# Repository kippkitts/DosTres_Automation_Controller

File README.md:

DosTres_Automation_Controller
=============================

The [DosTres Automation Controller](http://kippkitts.com/collections/frontpage/products/dostres-automation-controller-kk-m-23) is a shield for the Arduino Uno that allows you to control a number of high power devices.  It carries motor drivers to power 2 brush DC motors at 40v/5A as well as 3 MOSFET load switches to control high load devices (solenoids, lights, pumps, etc.).  The DosTres also allows you to drive a stepper motor in place of the DC motors.  The Eagle files for this board can be found here.

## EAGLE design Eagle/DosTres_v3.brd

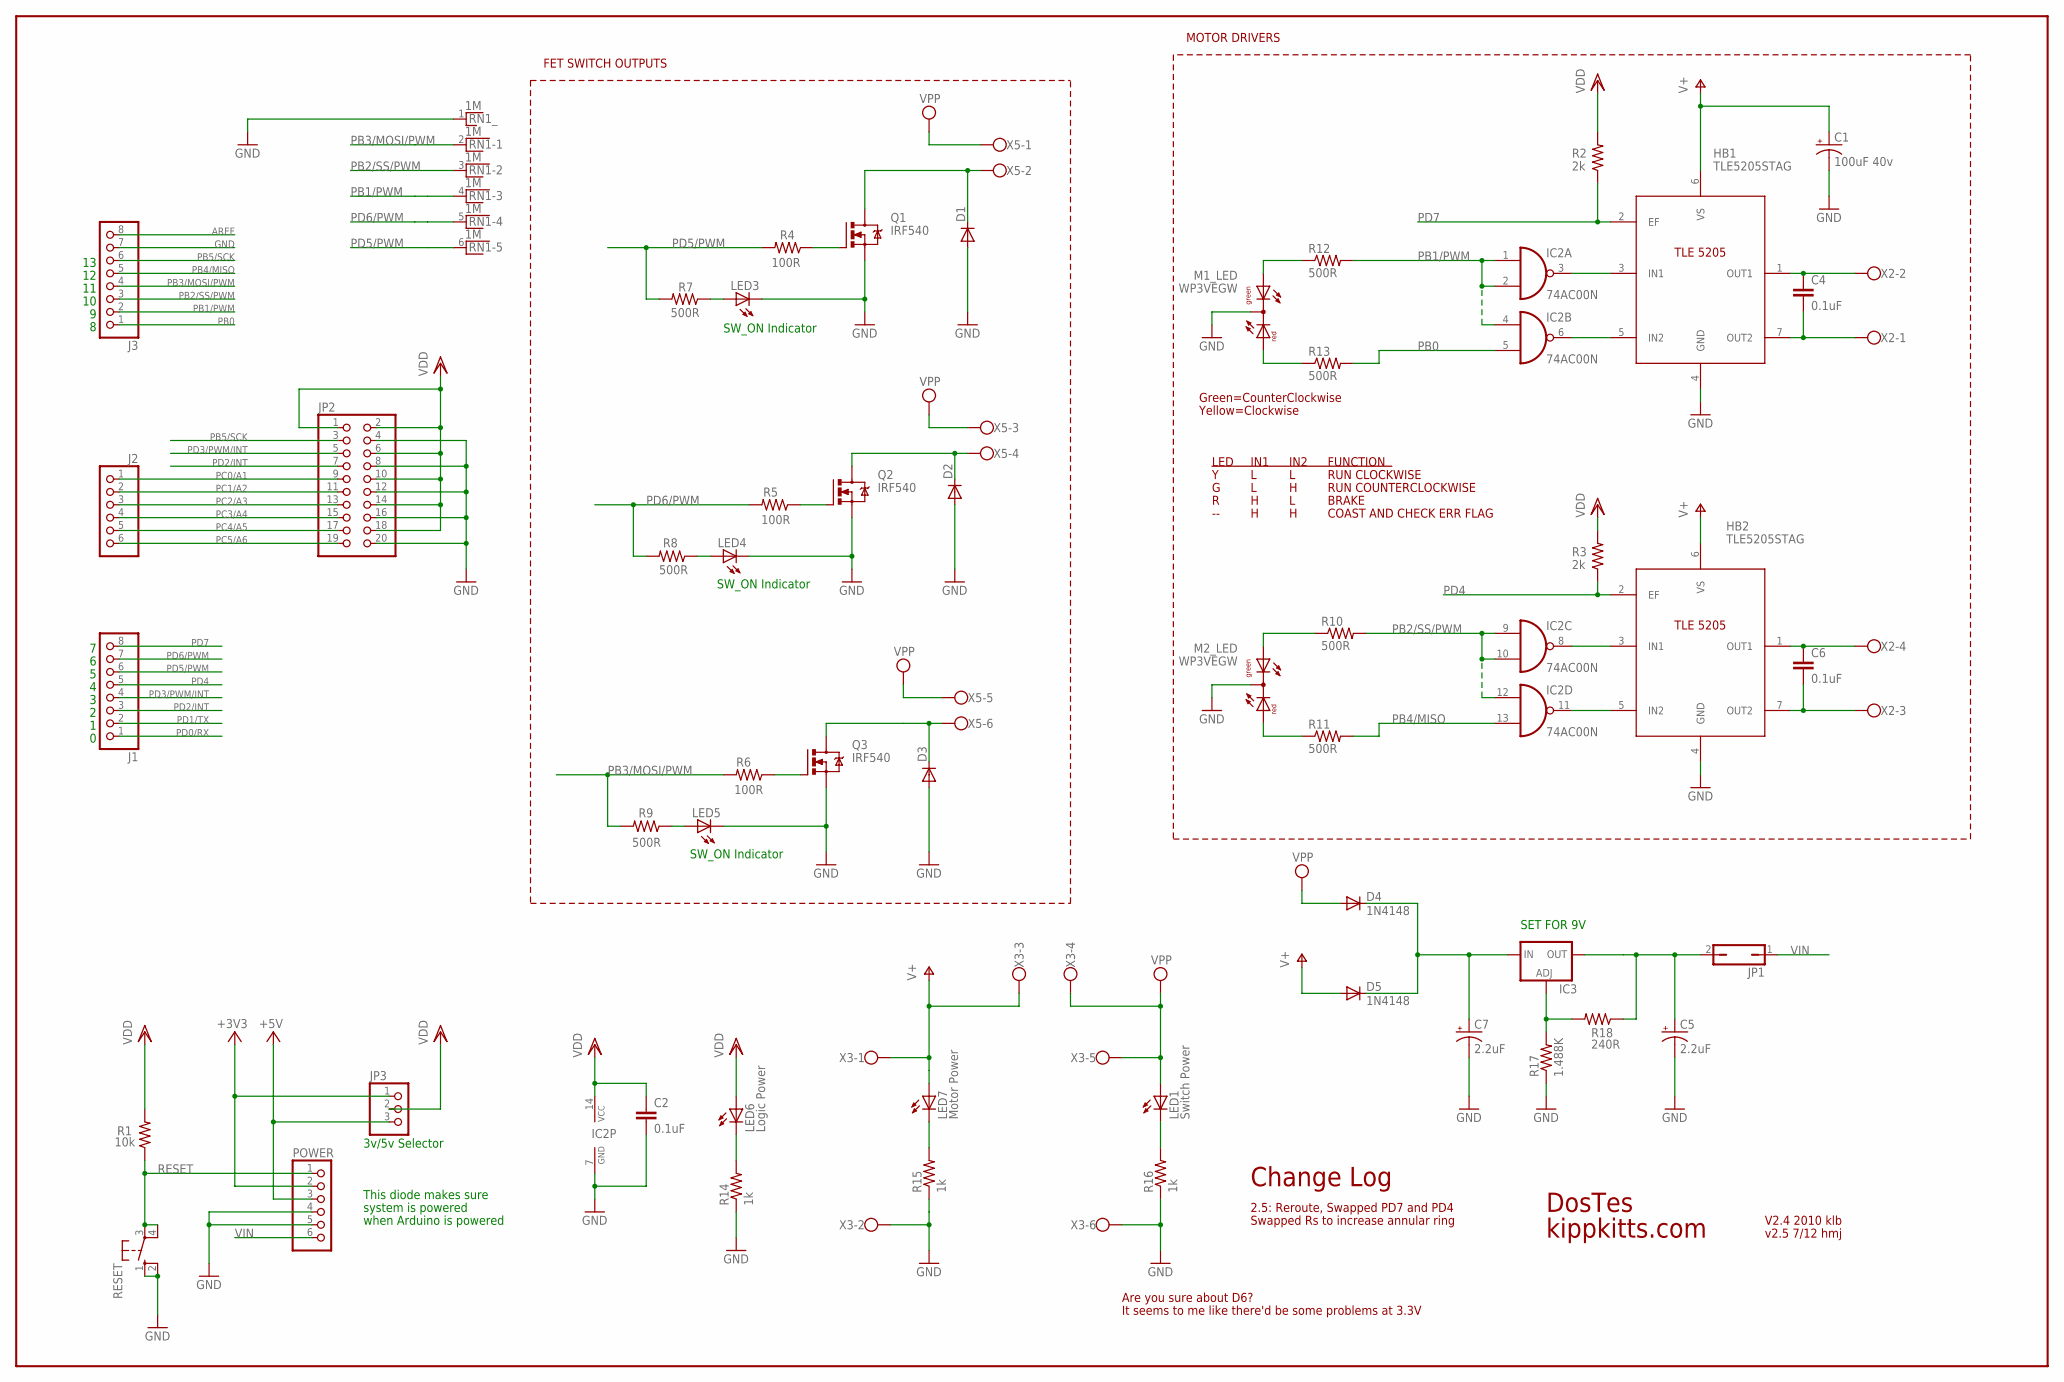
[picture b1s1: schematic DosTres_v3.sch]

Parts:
C1: 100uF 40v; E2,5-6E
C2, C4, C6: 0.1uF; CAP-PTH-SMALL-KIT
C5, C7: 2.2uF; CPOL-RADIAL-10UF-25V
D1, D2, D3: DIODE-1MMHOLED-7.5BH; D-7.5BH
D4, D5: 1N4148; D-7.5BH
HB1, HB2: TLE5205STAG; TO220-7-11
IC2: 74AC00N; DIL14
IC3: LM317TS; 317TS
J1, J3: PINHD-1X8; 1X08
J2: PINHD-1X6; 1X06
JP1: JP1Q; JP1
JP2: PINHD-2X10HAND; 2X10HAND
JP3: PINHD-1X3; 1X03
LED1: Switch Power; LED3MM
LED3, LED4, LED5: LED3MMX1MM3MM; LED3MM
LED6: Logic Power; LED3MM
LED7: Motor Power; LED3MM
M1_LED, M2_LED: WP3VEGW; DUOLED-A-3MM
POWER: PINHD-1X6; 1X06
Q1, Q2, Q3: IRF540; TO220BV
R1: 10k; 0207/2V
R2, R3: 2k; 0207/2V
R4, R5, R6: 100R; 0207/2V
R7, R8, R9, R10, R11, R12, R13: 500R; 0207/2V
R14, R15, R16: 1k; 0207/2V
R17: 1.488K; 0207/2V
R18: 240R; 0207/2V
RESET: 10-XX; B3F-10XX
RN1: 1M; RN-6
X2: W237-4
X3, X5: W237-6

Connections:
+3V3: JP3.1, POWER.2
+5V: JP3.3, POWER.3
AREF: J3.8
GND: C1.-, C2.2, C5.2 (-), C7.2 (-), D1.A, D2.A, D3.A, HB1.4 (GND), HB2.4 (GND), IC2.7 (GND), J3.7, JP2.4, JP2.8, JP2.12, JP2.16, JP2.20, LED3.K (C), LED4.K (C), LED5.K (C), M1_LED.2 (C), M2_LED.2 (C), POWER.4, POWER.5, Q1.S, Q2.S, Q3.S, R14.1, R15.1, R16.1, R17.1, RESET.1 (S), RESET.2 (S1), RN1.1, X3.2, X3.6
M1.1: C4.1, HB1.1 (OUT1), X2.2
M1.2: C4.2, HB1.7 (OUT2), X2.1
M2.1: C6.1, HB2.1 (OUT1), X2.4
M2.2: C6.2, HB2.7 (OUT2), X2.3
unnamed: Q1.G, R4.1
unnamed: Q2.G, R5.1
unnamed: Q3.G, R6.1
unnamed: M1_LED.3 (AG), R12.1
unnamed: HB1.3 (IN1), IC2.3 (O)
unnamed: HB1.5 (IN2), IC2.6 (O)
unnamed: HB2.3 (IN1), IC2.8 (O)
unnamed: HB2.5 (IN2), IC2.11 (O)
unnamed: M1_LED.1 (AR), R13.1
unnamed: D3.C, Q3.D, X5.6
unnamed: D2.C, Q2.D, X5.4
unnamed: M2_LED.1 (AR), R11.1
unnamed: M2_LED.3 (AG), R10.1
unnamed: D1.C, Q1.D, X5.2
unnamed: C7.1 (+), D4.C, D5.C, IC3.3 (IN)
unnamed: LED3.A, R7.1
unnamed: LED4.A, R8.1
unnamed: LED5.A, R9.1
unnamed: C5.1 (+), IC3.2 (OUT), JP1.2, R18.1
unnamed: IC3.1 (ADJ), R17.2, R18.2
unnamed: LED6.K (C), R14.2
unnamed: LED7.K (C), R15.2
unnamed: LED1.K (C), R16.2
PB0: IC2.5 (I1), J3.1, R13.2
PB1/PWM: IC2.1 (I0), IC2.2 (I1), IC2.4 (I0), J3.2, R12.2, RN1.4
PB2/SS/PWM: IC2.9 (I0), IC2.10 (I1), IC2.12 (I0), J3.3, R10.2, RN1.3
PB3/MOSI/PWM: J3.4, R6.2, R9.2, RN1.2
PB4/MISO: IC2.13 (I1), J3.5, R11.2
PB5/SCK: J3.6, JP2.3
PC0/A1: J2.1, JP2.9
PC1/A2: J2.2, JP2.11
PC2/A3: J2.3, JP2.13
PC3/A4: J2.4, JP2.15
PC4/A5: J2.5, JP2.17
PC5/A6: J2.6, JP2.19
PD0/RX: J1.1
PD1/TX: J1.2
PD2/INT: J1.3, JP2.7
PD3/PWM/INT: J1.4, JP2.5
PD4: HB2.2 (EF), J1.5, R3.1
PD5/PWM: J1.6, R4.2, R7.2, RN1.6
PD6/PWM: J1.7, R5.2, R8.2, RN1.5
PD7: HB1.2 (EF), J1.8, R2.1
RESET: POWER.1, R1.1, RESET.3, RESET.4 (P1)
V+: C1.+, D5.A, HB1.6 (VS), HB2.6 (VS), LED7.A, X3.1, X3.3
VDD: C2.1, IC2.14 (VCC), JP2.1, JP2.2, JP2.6, JP2.10, JP2.14, JP2.18, JP3.2, LED6.A, R1.2, R2.2, R3.2
VIN: JP1.1, POWER.6
VPP: D4.A, LED1.A, X3.4, X3.5, X5.1, X5.3, X5.5

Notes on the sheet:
Green=CounterClockwise
Yellow=Clockwise
SET FOR 9V
3v/5v Selector
SW_ON Indicator
This diode makes sure
when Arduino is powered
FET SWITCH OUTPUTS
IN1
IN2
FUNCTION
RUN CLOCKWISE
RUN COUNTERCLOCKWISE
BRAKE
COAST AND CHECK ERR FLAG
LED
MOTOR DRIVERS
system is powered
2.5: Reroute, Swapped PD7 and PD4
Change Log
DosTes
kippkitts.com
v2.5 7/12 hmj
Swapped Rs to increase annular ring
V2.4 2010 klb
Are you sure about D6?
It seems to me like there'd be some problems at 3.3V

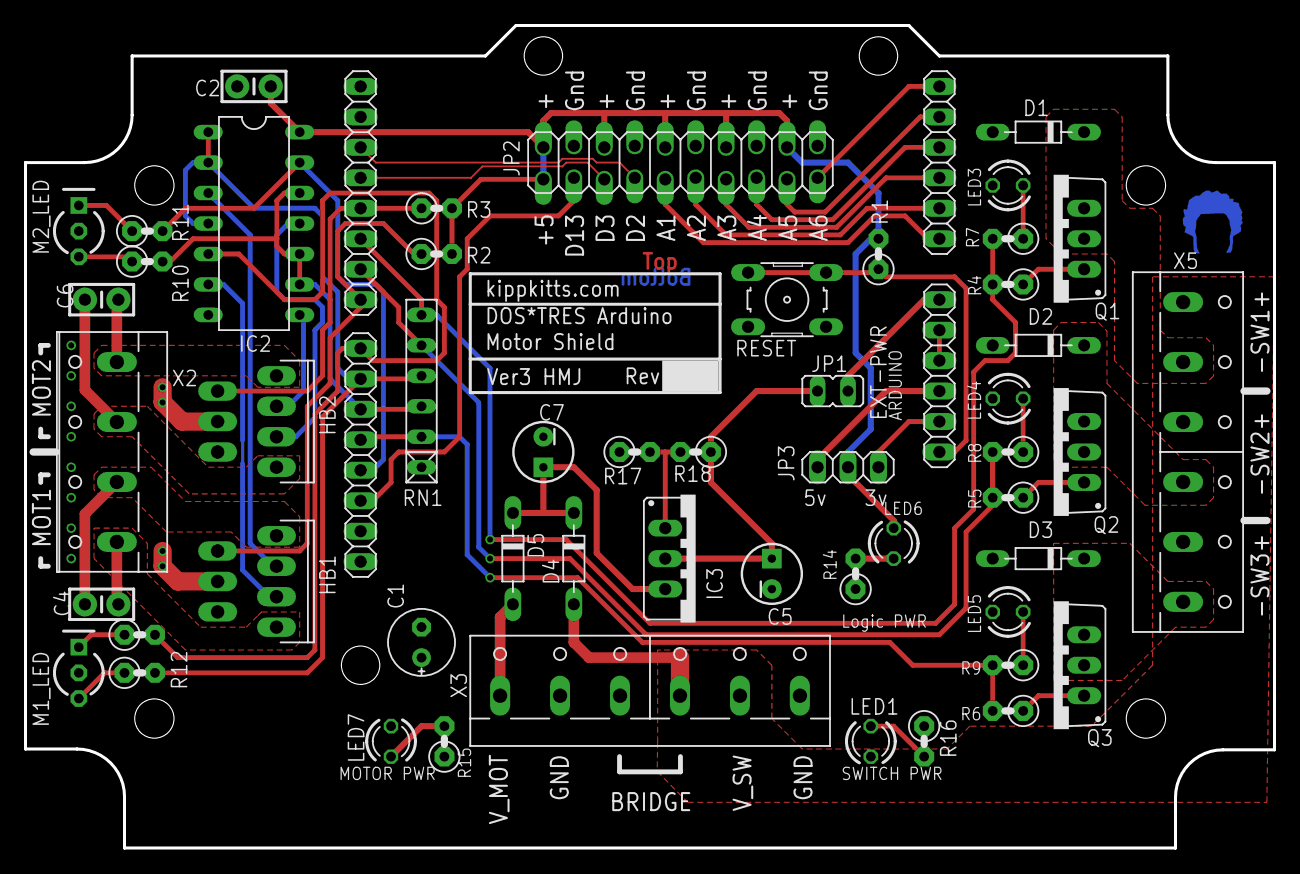
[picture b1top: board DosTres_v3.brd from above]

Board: 2 copper layers, 104.1 x 68.6 mm, 58 parts (1 on the bottom side), 53 nets.

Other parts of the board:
U$1: TOP_DOCU_5MM
U$3: COPPER_5MM

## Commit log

2014-03-26 Create Repository
2014-04-29 Upload Arduino Code

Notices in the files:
parts and their libraries:
SparkFun: Licensing: CC v3.0 Share-Alike You are welcome to use this library for commercial purposes.
